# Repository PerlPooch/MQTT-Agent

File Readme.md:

# Spencer MQTT Agent

Please see the [Project Website](https://home.marcspencer.com/mqtt-agent/) for detailed information, full API, and build details. 

## MQTT Topic

	spencer/<ID>/<device>
		<ID> := unique MAC address of device
		<device> := temperature|status|relay
		
## Payload (JSON object):

	{
		"command": "fetch"|"set-rate"|"set"
		"rate": int: seconds between updates|duration
		"device-num": int: 0-based index of device 
		"state": "on"|"off"|"pulse"
	}

	command == "fetch"
		Causes agent to publish information for <device>

	command == "set-rate"
		Sets update rate for <device> to rate in rate. <device> can be temperature, status or relay

	command == "set"
		Sets <device> at index device-num to state. <device> can be relay. <state> can be on, off, or pulse.
		
## Examples:

	spencer/FC:F5:C4:AB:56:24/temperature {"command":"set-rate", "rate":"120"}
		Set the update rate for temperature reports to be 120 seconds

	spencer/FC:F5:C4:AB:56:24/status {"command":"set-rate", "rate":"300"}
		Set the update rate for status reports to be 300 seconds

	spencer/FC:F5:C4:AB:56:24/relay {"command":"set", "device-num":"1", "state":"on"}
		Turn on relay 0

	spencer/FC:F5:C4:AB:56:24/relay {"command":"set", "device-num":"1", "state":"off"}
		Turn off relay 1

	spencer/FC:F5:C4:AB:56:24/relay {"command":"set", "device-num":"0", "state":"pulse"}
		Pulse relay 0

	spencer/FC:F5:C4:AB:56:24/relay {"command":"set-rate", "rate":"200"}
		Set relay pulse duration to 100ms

	spencer/FC:F5:C4:AB:56:24/temperature {"command":"fetch"}
		Request publish of temperature

	spencer/FC:F5:C4:AB:56:24/status {"command":"fetch"}
		Request publish of input status

	spencer/FC:F5:C4:AB:56:24/relay {"command":"fetch"}
		Request publish of relay status

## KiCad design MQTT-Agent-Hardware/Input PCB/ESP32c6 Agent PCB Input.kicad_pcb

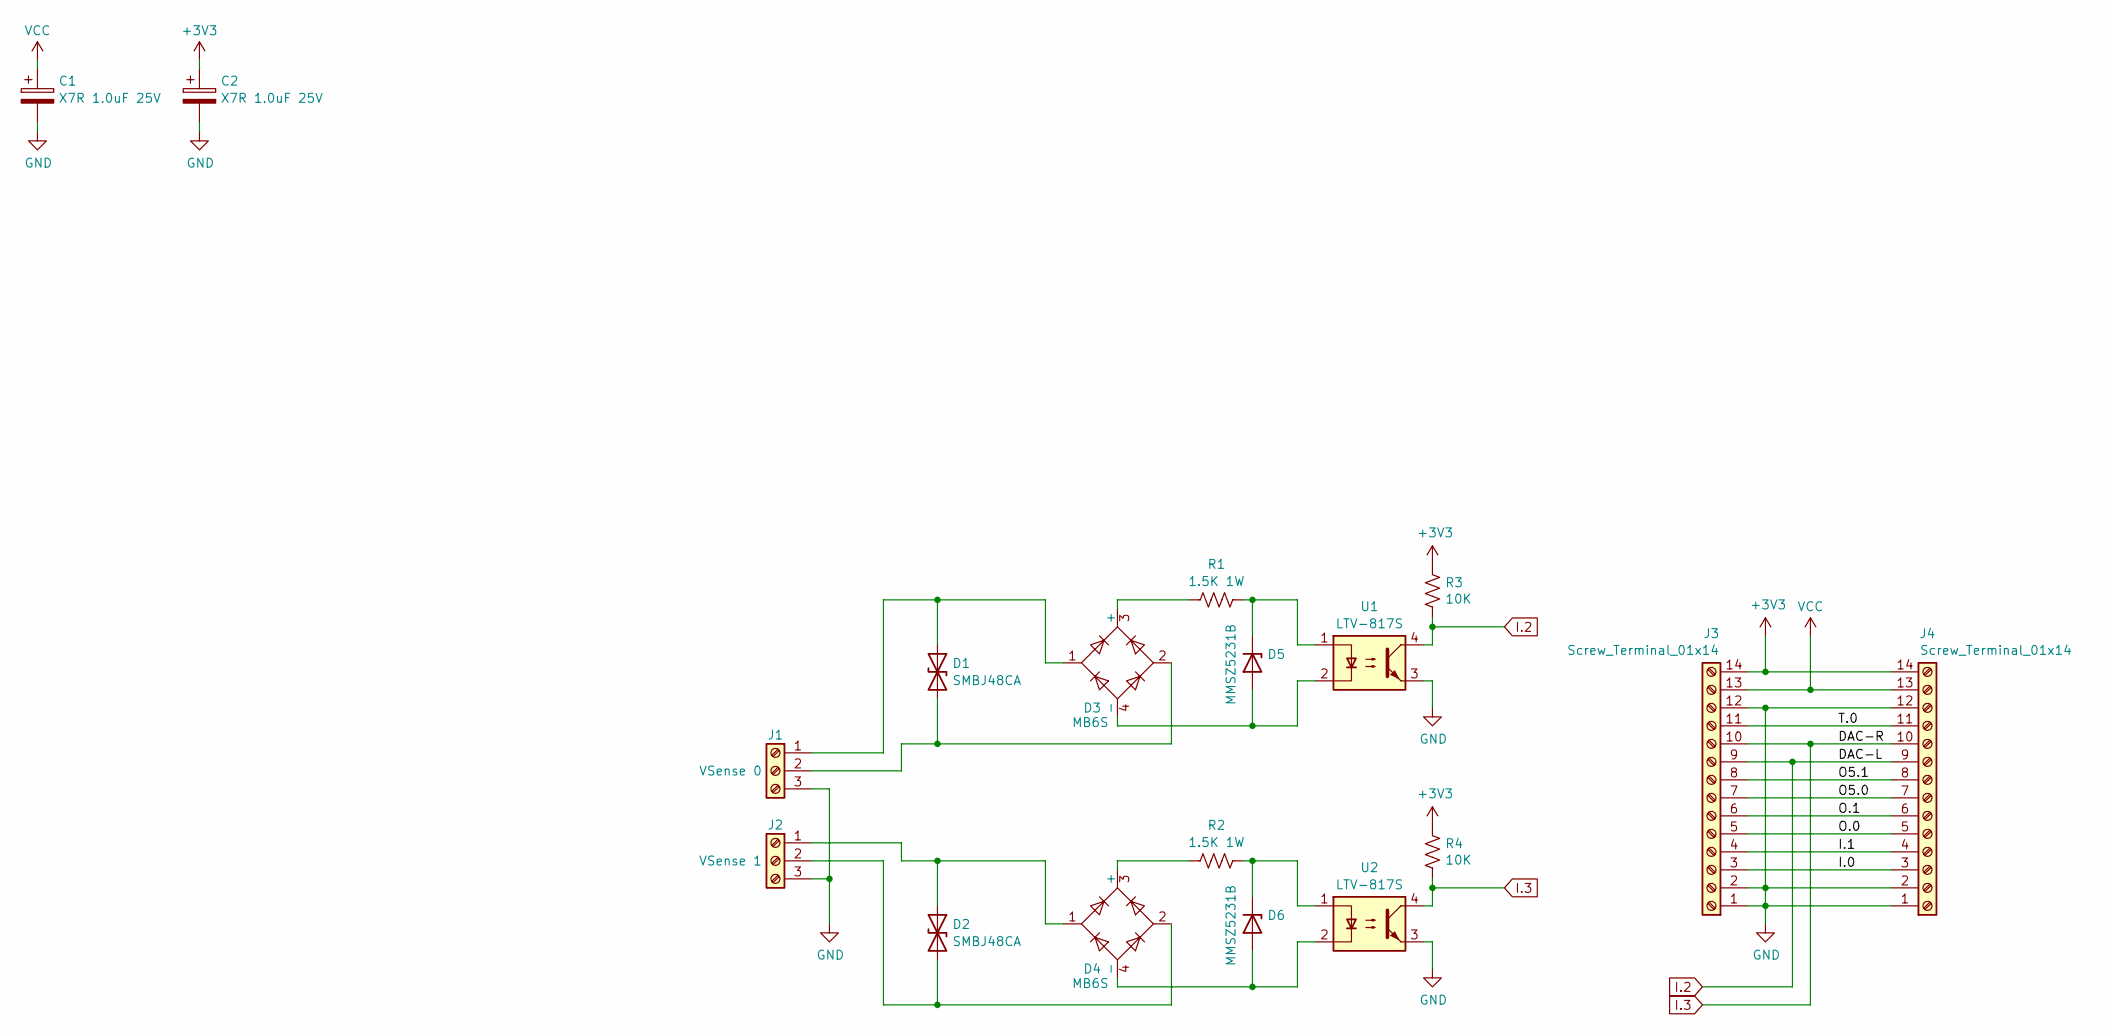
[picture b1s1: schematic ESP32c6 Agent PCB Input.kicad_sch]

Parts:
C1, C2: X7R 1.0uF 25V; C_0805_2012Metric_Pad1.18x1.45mm_HandSolder
D1, D2: SMBJ48CA; D_SMB
D3, D4: MB6S; TO-269AA
D5, D6: MMSZ5231B; Nexperia_CFP3_SOD-123W
J1: VSense 0; Molex_KK-254_AE-6410-03A_1x03_P2.54mm_Vertical
J2: VSense 1; Molex_KK-254_AE-6410-03A_1x03_P2.54mm_Vertical
J3: Screw_Terminal_01x14; Connector SIP-14-Soldertail-L
J4: Screw_Terminal_01x14; Connector SIP-14-Soldertail-R
R1, R2: 1.5K 1W; R_2512_6332Metric_Pad1.40x3.35mm_HandSolder
R3, R4: 10K; R_1206_3216Metric_Pad1.30x1.75mm_HandSolder
U1, U2: LTV-817S; SMDIP-4_W9.53mm

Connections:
+3V3: C2.1, J3.14, J4.14, R3.1, R4.1
/I.0: J3.3, J4.3
/I.1: J3.4, J4.4
/O5.0: J3.7, J4.7
/O5.1: J3.8, J4.8
/O.0: J3.5, J4.5
/O.1: J3.6, J4.6
/T.0: J3.11, J4.11
GND: C1.2, C2.2, J1.3, J2.3, J3.1, J3.2, J3.12, J4.1, J4.2, J4.12, U1.3, U2.3
I.2: J3.9, J4.9, R3.2, U1.4
I.3: J3.10, J4.10, R4.2, U2.4
unnamed: D1.1 (A1), D3.1, J1.1
unnamed: D1.2 (A2), D3.2, J1.2
unnamed: D2.1 (A1), D4.1, J2.1
unnamed: D2.2 (A2), D4.2, J2.2
unnamed: D3.3 (+), R1.1
unnamed: D3.4 (-), D5.2 (A), U1.2
unnamed: D4.3 (+), R2.1
unnamed: D4.4 (-), D6.2 (A), U2.2
unnamed: D5.1 (K), R1.2, U1.1
unnamed: D6.1 (K), R2.2, U2.1
VCC: C1.1, J3.13, J4.13

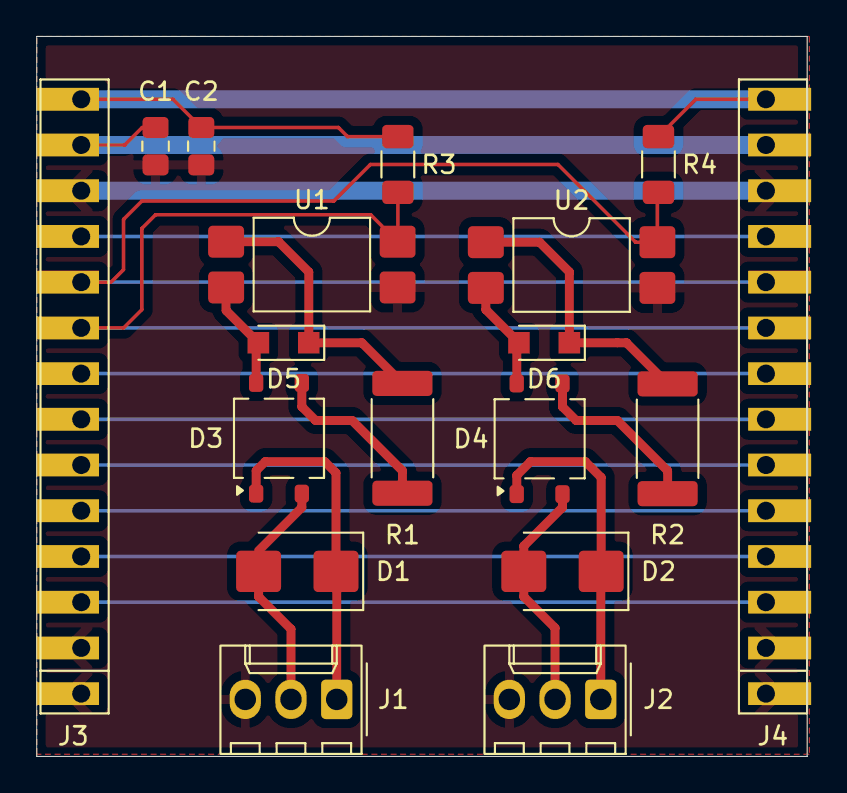
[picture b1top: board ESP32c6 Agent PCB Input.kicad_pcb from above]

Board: 2 copper layers, 42.8 x 40.0 mm, 18 parts (0 on the bottom side), 22 nets.

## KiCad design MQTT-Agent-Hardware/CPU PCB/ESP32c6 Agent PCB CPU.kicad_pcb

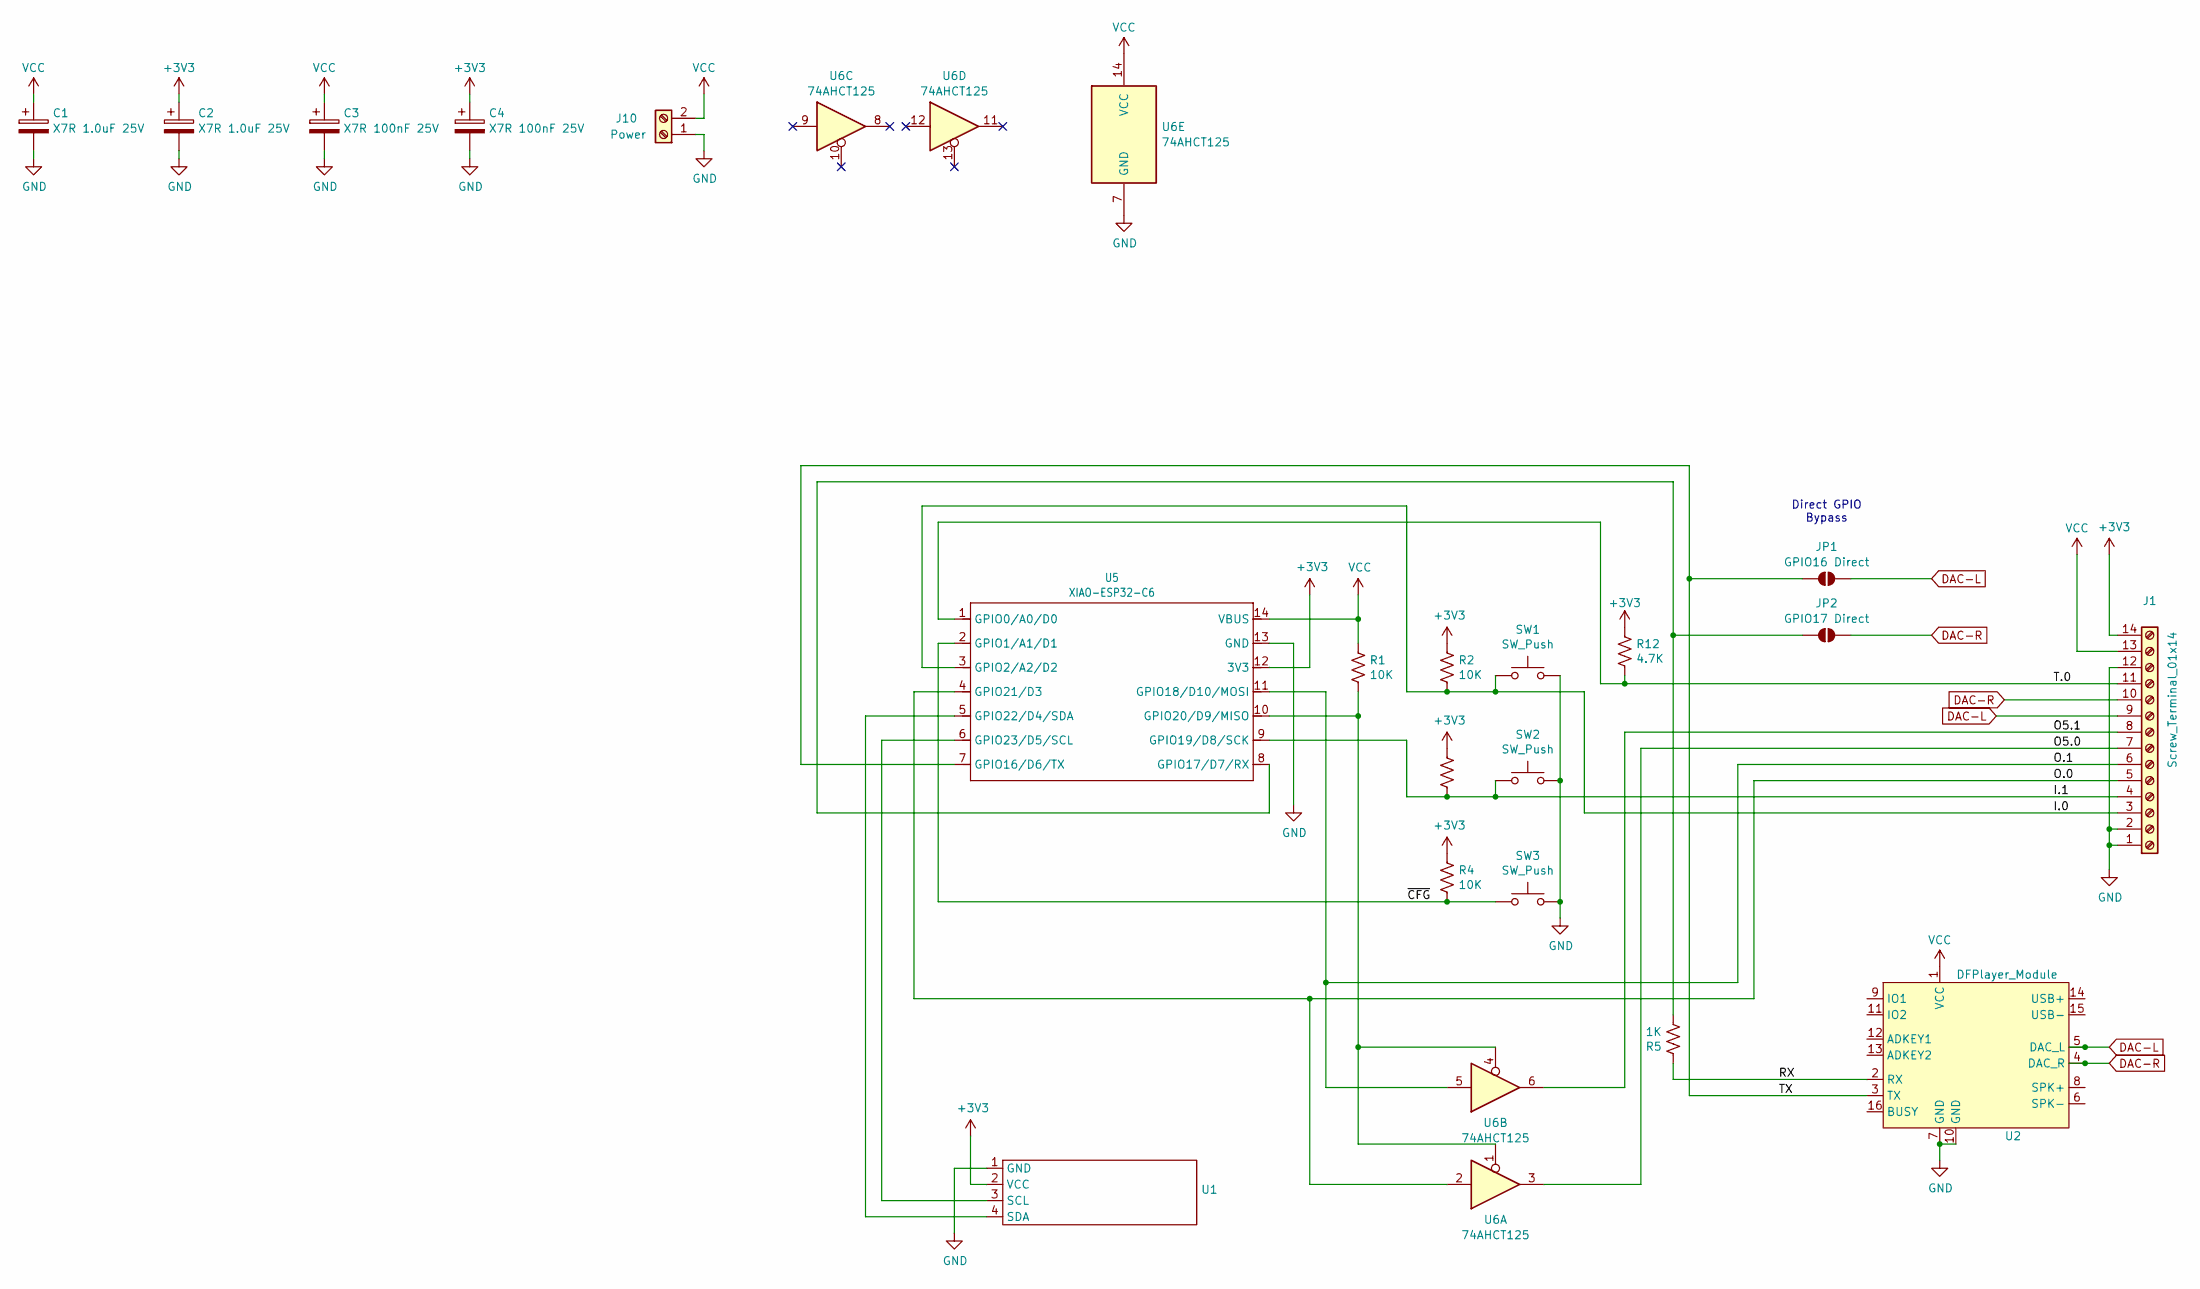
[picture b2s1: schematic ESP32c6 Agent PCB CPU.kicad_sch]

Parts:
C1, C2: X7R 1.0uF 25V; C_0805_2012Metric_Pad1.18x1.45mm_HandSolder
C3, C4: X7R 100nF 25V; C_1206_3216Metric_Pad1.33x1.80mm_HandSolder
J1: Screw_Terminal_01x14; Connector SIP-14-Soldertail-R
J10: Power; Molex_KK-254_AE-6410-02A_1x02_P2.54mm_Vertical
JP1: GPIO16 Direct; SolderJumper-2_P1.3mm_Open_Pad1.0x1.5mm
JP2: GPIO17 Direct; SolderJumper-2_P1.3mm_Open_Pad1.0x1.5mm
R1, R2, R3, R4: 10K; R_1206_3216Metric_Pad1.30x1.75mm_HandSolder
R5: 1K; R_1206_3216Metric_Pad1.30x1.75mm_HandSolder
R12: 4.7K; R_1206_3216Metric_Pad1.30x1.75mm_HandSolder
SW1, SW2, SW3: SW_Push; SW_PUSH_6mm_H4.3mm
U1: SSD1306-128x32_Borderless
U2: DFPlayer_Module; DFPlayer
U5: XIAO-ESP32-C6; XIAO-ESP32C6-DIP
U6: 74AHCT125; SSOP-14_5.3x6.2mm_P0.65mm

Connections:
+3V3: C2.1, C4.1, J1.14, R2.1, R3.1, R4.1, R12.1, U1.2 (VCC), U5.12 (3V3)
/I.0: J1.3, R2.2, SW1.1, U5.3 (GPIO2/A2/D2)
/I.1: J1.4, R3.2, SW2.1, U5.9 (GPIO19/D8/SCK)
/O5.0: J1.7, U6.3
/O5.1: J1.8, U6.6
/O.0: J1.5, U5.4 (GPIO21/D3), U6.2
/O.1: J1.6, U5.11 (GPIO18/D10/MOSI), U6.5
/RX: R5.1, U2.2 (RX)
/T.0: J1.11, R12.2, U5.1 (GPIO0/A0/D0)
/TX: JP1.1 (A), U2.3 (TX), U5.7 (GPIO16/D6/TX)
/~CFG: R4.2, SW3.1, U5.2 (GPIO1/A1/D1)
DAC-L: J1.9, JP1.2 (B), U2.5 (DAC_L)
DAC-R: J1.10, JP2.2 (B), U2.4 (DAC_R)
GND: C1.2, C2.2, C3.2, C4.2, J1.1, J1.2, J1.12, J10.1, SW1.2, SW2.2, SW3.2, U1.1 (GND), U2.7 (GND), U2.10 (GND), U5.13 (GND), U6.7 (GND)
unnamed: JP2.1 (A), R5.2, U5.8 (GPIO17/D7/RX)
unnamed: U1.3 (SCL), U5.6 (GPIO23/D5/SCL)
unnamed: U1.4 (SDA), U5.5 (GPIO22/D4/SDA)
unnamed: R1.2, U5.10 (GPIO20/D9/MISO), U6.1, U6.4
VCC: C1.1, C3.1, J1.13, J10.2, R1.1, U2.1 (VCC), U5.14 (VBUS), U6.14 (VCC)

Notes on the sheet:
Direct GPIO Bypass

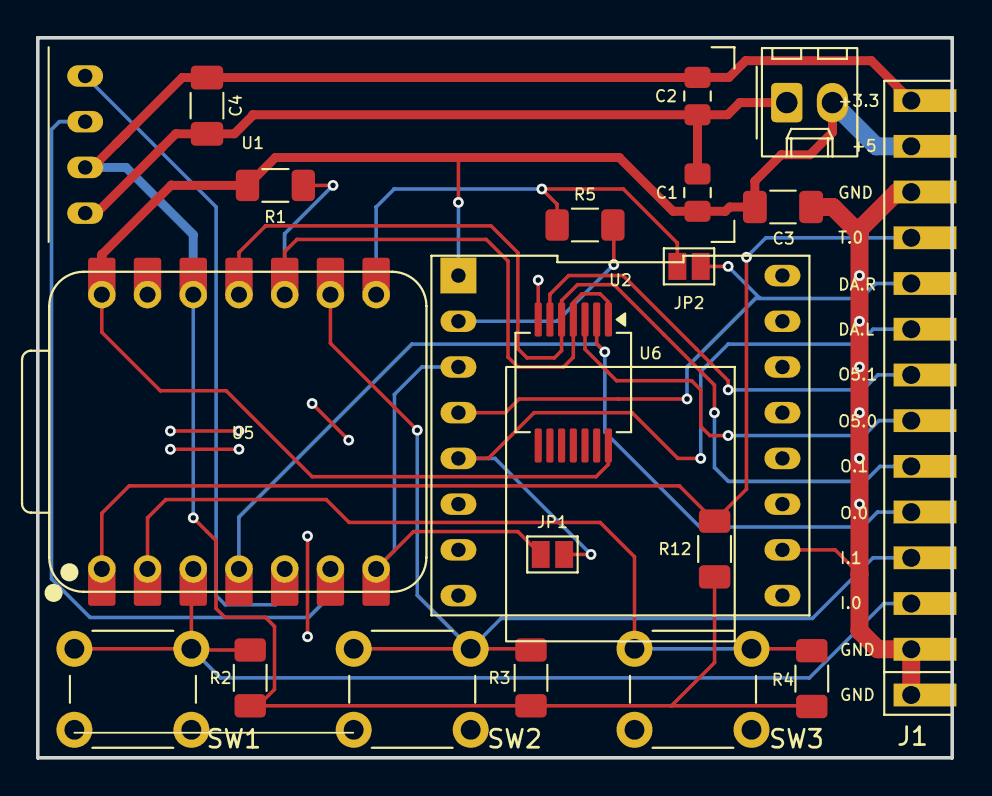
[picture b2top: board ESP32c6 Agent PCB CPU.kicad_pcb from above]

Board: 2 copper layers, 50.8 x 40.0 mm, 21 parts (0 on the bottom side), 19 nets.

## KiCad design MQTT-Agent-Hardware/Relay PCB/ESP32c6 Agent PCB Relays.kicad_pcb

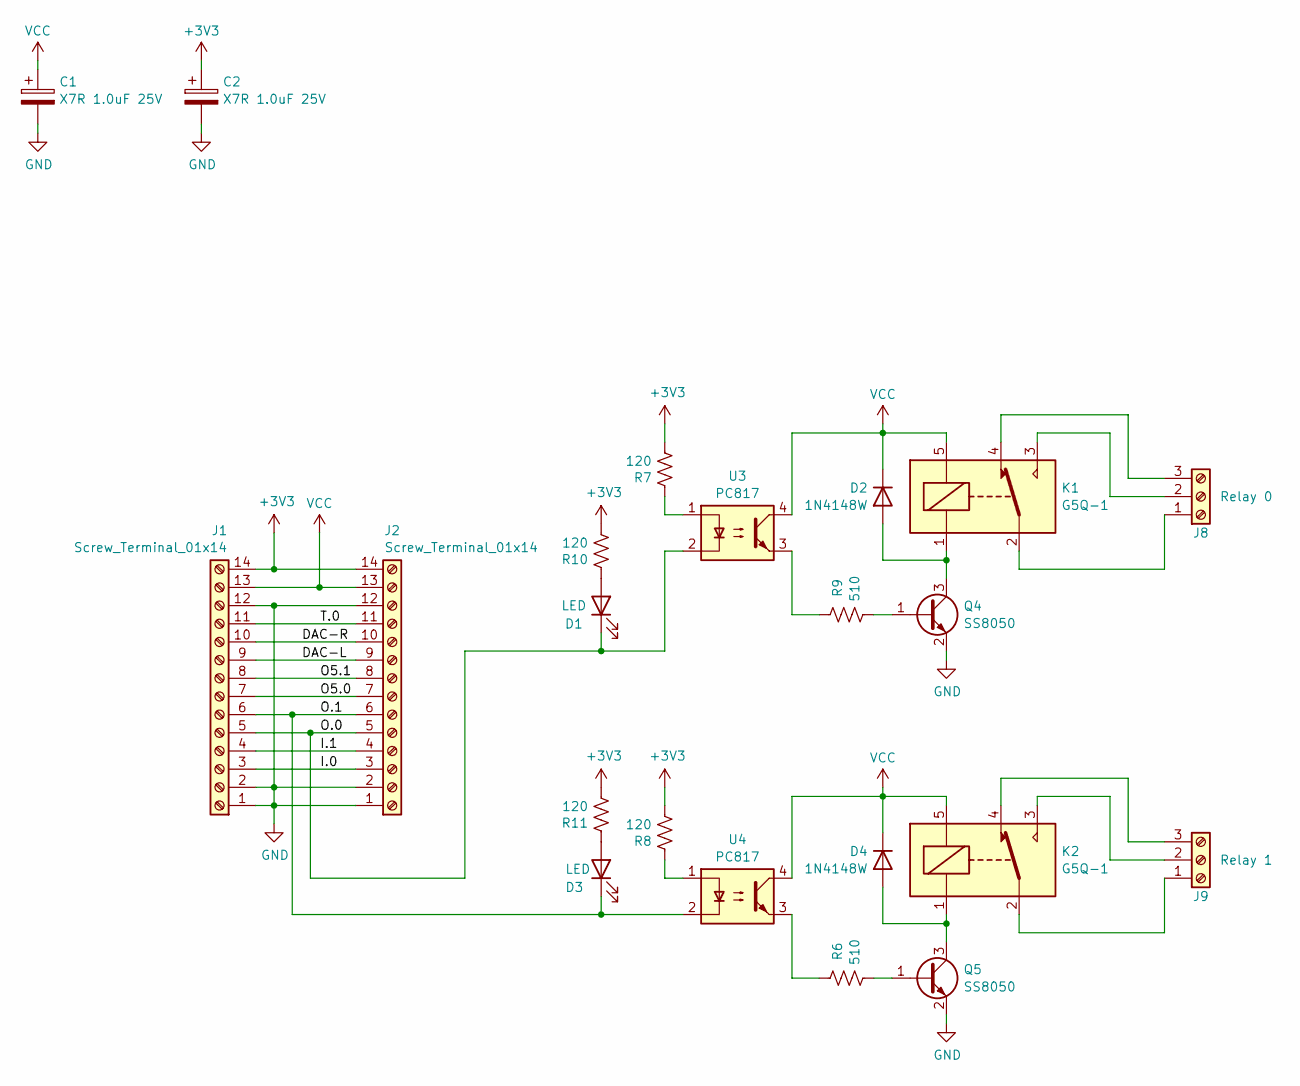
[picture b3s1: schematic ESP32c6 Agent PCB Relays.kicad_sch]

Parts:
C1, C2: X7R 1.0uF 25V; C_0805_2012Metric_Pad1.18x1.45mm_HandSolder
D1, D3: LED; LED_1206_3216Metric_Pad1.42x1.75mm_HandSolder
D2, D4: 1N4148W; D_SOD-123
J1: Screw_Terminal_01x14; Connector SIP-14-Soldertail-L
J2: Screw_Terminal_01x14; Connector SIP-14-Soldertail-R
J8: Relay 0; Molex_KK-254_AE-6410-03A_1x03_P2.54mm_Vertical
J9: Relay 1; Molex_KK-254_AE-6410-03A_1x03_P2.54mm_Vertical
K1, K2: G5Q-1; Relay_SPDT_Omron-G5Q-1
Q4, Q5: SS8050; SOT-23
R6, R9: 510; R_1206_3216Metric_Pad1.30x1.75mm_HandSolder
R7, R8, R10, R11: 120; R_1206_3216Metric_Pad1.30x1.75mm_HandSolder
U3, U4: PC817; DIP-4_W7.62mm

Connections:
+3V3: C2.1, J1.14, J2.14, R7.2, R8.2, R10.2, R11.2
/DAC-L: J1.9, J2.9
/DAC-R: J1.10, J2.10
/I.0: J1.3, J2.3
/I.1: J1.4, J2.4
/O5.0: J1.7, J2.7
/O5.1: J1.8, J2.8
/O.0: D1.1 (K), J1.5, J2.5, U3.2
/O.1: D3.1 (K), J1.6, J2.6, U4.2
/T.0: J1.11, J2.11
GND: C1.2, C2.2, J1.1, J1.2, J1.12, J2.1, J2.2, J2.12, Q4.2 (E), Q5.2 (E)
unnamed: D1.2 (A), R10.1
unnamed: D2.2 (A), K1.1, Q4.3 (C)
unnamed: D3.2 (A), R11.1
unnamed: D4.2 (A), K2.1, Q5.3 (C)
unnamed: J8.1, K1.2
unnamed: J8.2, K1.3
unnamed: J8.3, K1.4
unnamed: J9.1, K2.2
unnamed: J9.2, K2.3
unnamed: J9.3, K2.4
unnamed: Q4.1 (B), R9.2
unnamed: Q5.1 (B), R6.2
unnamed: R6.1, U4.3
unnamed: R7.1, U3.1
unnamed: R8.1, U4.1
unnamed: R9.1, U3.3
VCC: C1.1, D2.1 (K), D4.1 (K), J1.13, J2.13, K1.5, K2.5, U3.4, U4.4

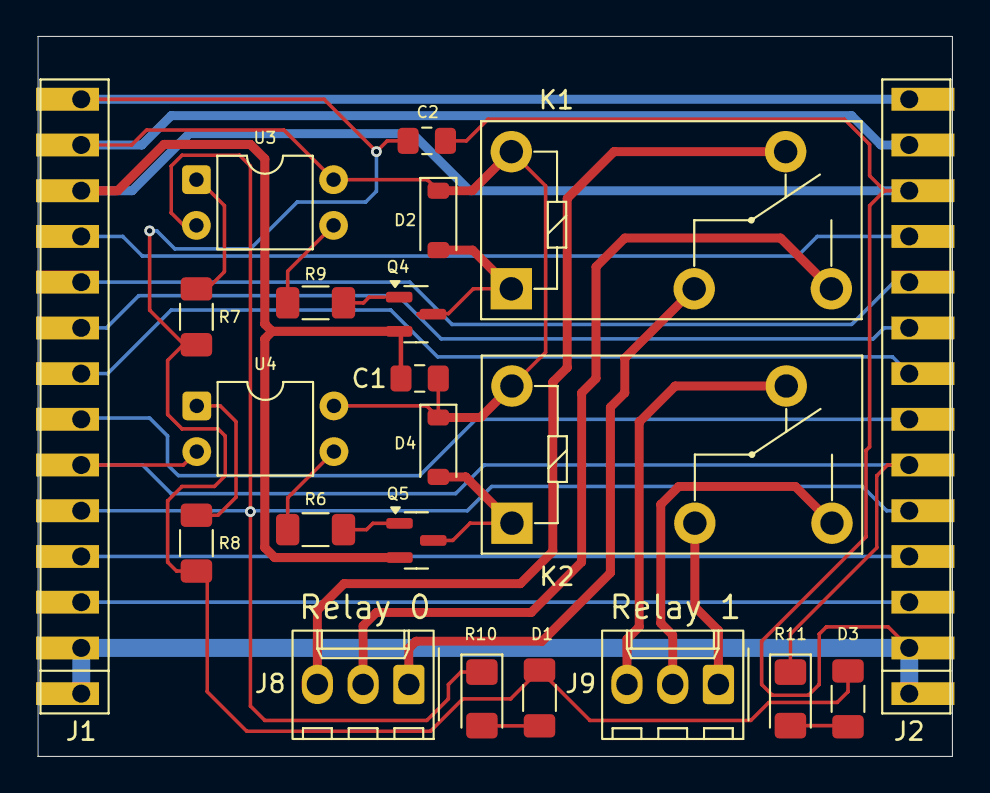
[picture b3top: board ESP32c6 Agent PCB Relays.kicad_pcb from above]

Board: 2 copper layers, 50.8 x 40.0 mm, 22 parts (0 on the bottom side), 28 nets.

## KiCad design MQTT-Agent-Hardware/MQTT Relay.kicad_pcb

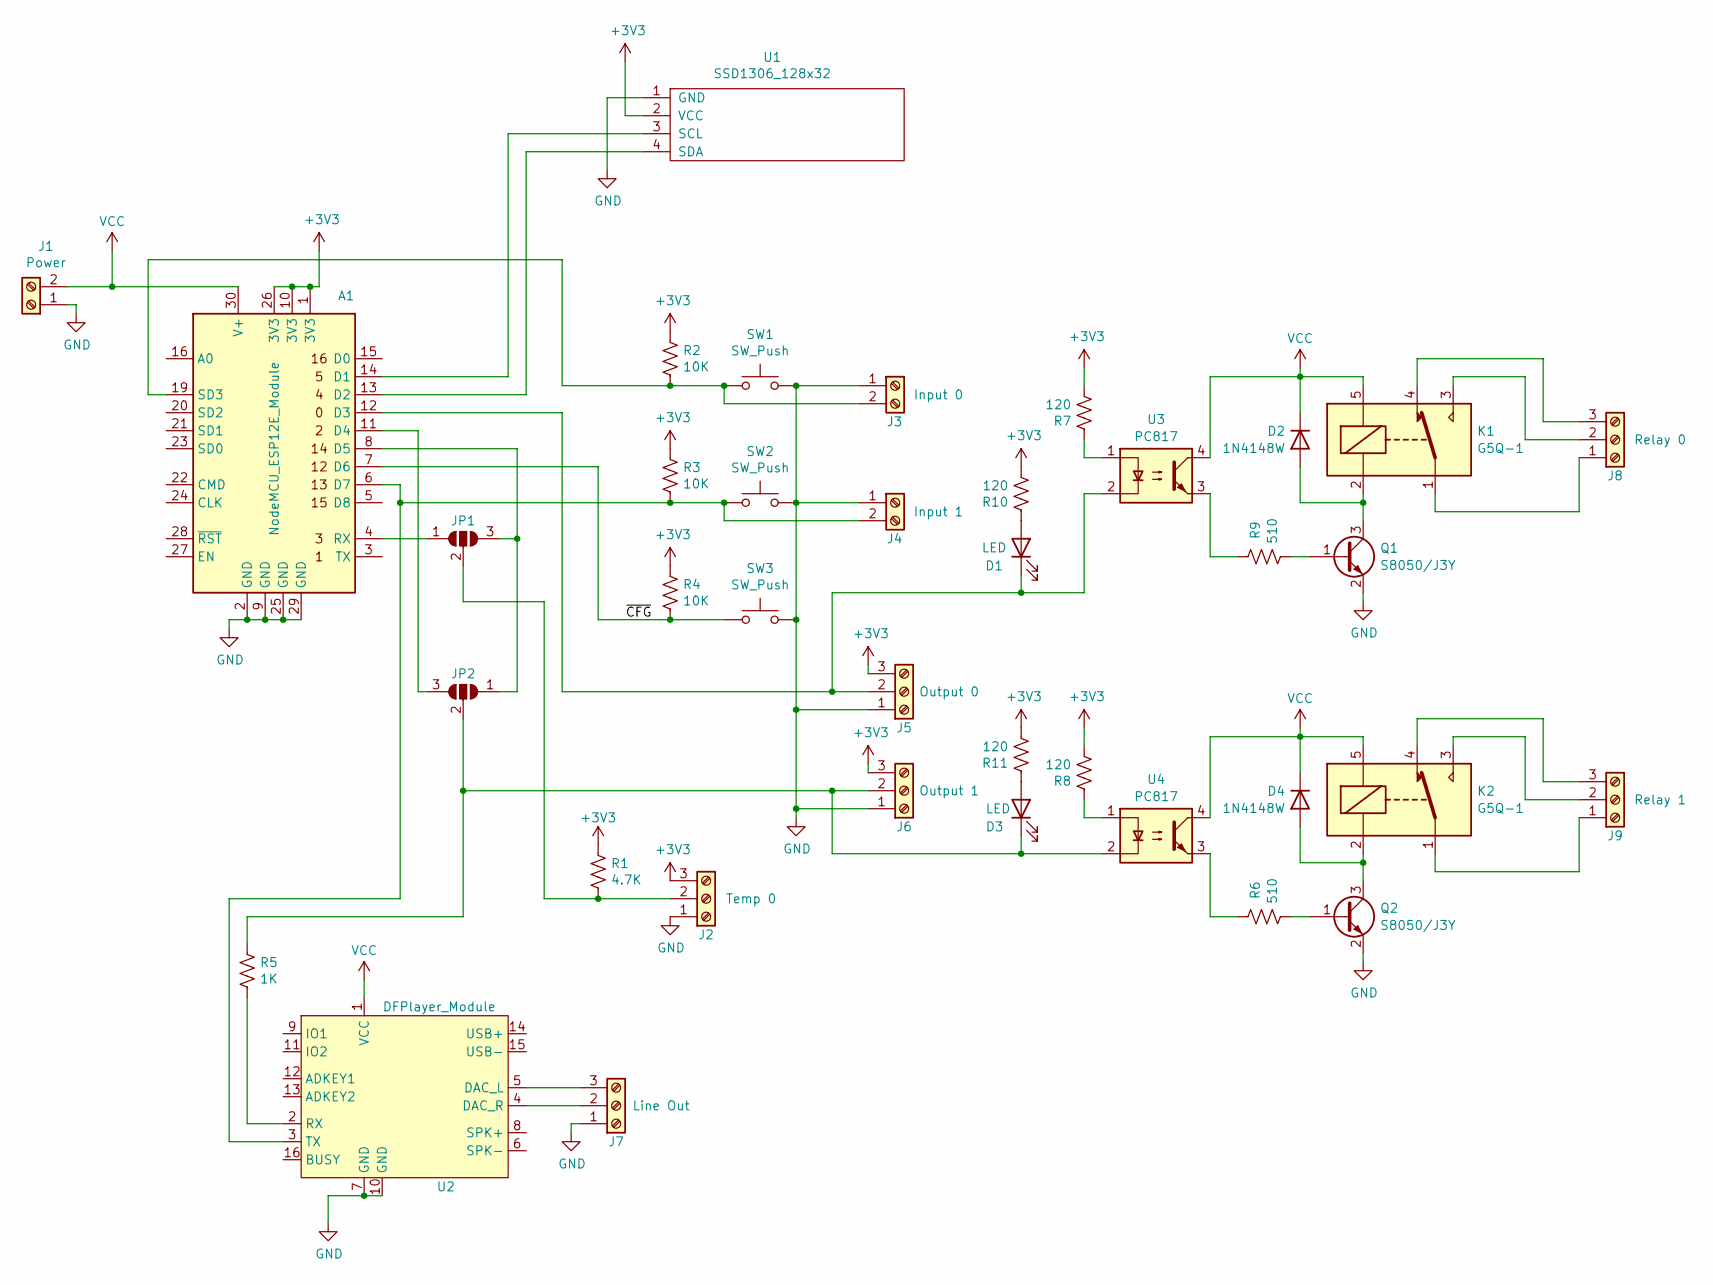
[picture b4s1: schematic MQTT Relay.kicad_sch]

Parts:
A1: NodeMCU_ESP12E_Module; NodeMCU
D1, D3: LED; LED_1206_3216Metric_Pad1.42x1.75mm_HandSolder
D2, D4: 1N4148W; D_SOD-123
J1: Power; TerminalBlock_Phoenix_MPT-0,5-2-2.54_1x02_P2.54mm_Horizontal
J2: Temp 0; TerminalBlock_Phoenix_MPT-0,5-3-2.54_1x03_P2.54mm_Horizontal
J3: Input 0; TerminalBlock_Phoenix_MPT-0,5-2-2.54_1x02_P2.54mm_Horizontal
J4: Input 1; TerminalBlock_Phoenix_MPT-0,5-2-2.54_1x02_P2.54mm_Horizontal
J5: Output 0; TerminalBlock_Phoenix_MPT-0,5-3-2.54_1x03_P2.54mm_Horizontal
J6: Output 1; TerminalBlock_Phoenix_MPT-0,5-3-2.54_1x03_P2.54mm_Horizontal
J7: Line Out; TerminalBlock_Phoenix_MPT-0,5-3-2.54_1x03_P2.54mm_Horizontal
J8: Relay 0; TerminalBlock_Phoenix_MPT-0,5-3-2.54_1x03_P2.54mm_Horizontal
J9: Relay 1; TerminalBlock_Phoenix_MPT-0,5-3-2.54_1x03_P2.54mm_Horizontal
JP1: T-0; SolderJumper-3_P1.3mm_Open_Pad1.0x1.5mm_NumberLabels
JP2: R-1; SolderJumper-3_P1.3mm_Open_Pad1.0x1.5mm_NumberLabels
K1, K2: G5Q-1; Relay_SPDT_SANYOU_SRD_Series_Form_C
Q1, Q2: S8050/J3Y; SOT-23-3
R1: 4.7K; R_1206_3216Metric_Pad1.30x1.75mm_HandSolder
R2, R3, R4: 10K; R_1206_3216Metric_Pad1.30x1.75mm_HandSolder
R5: 1K; R_1206_3216Metric_Pad1.30x1.75mm_HandSolder
R6, R9: 510; R_1206_3216Metric_Pad1.30x1.75mm_HandSolder
R7, R8, R10, R11: 120; R_1206_3216Metric_Pad1.30x1.75mm_HandSolder
SW1, SW2, SW3: SW_Push; SW_PUSH_6mm_H4.3mm
U1: SSD1306_128x32; PinHeader_1x04_P2.54mm_Vertical
U2: DFPlayer_Module; Module_DIP16_17.8mm
U3, U4: PC817; DIP-4_W7.62mm

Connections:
+3V3: A1.1 (3V3), A1.10 (3V3), A1.26 (3V3), J2.3, J5.3, J6.3, R1.1, R2.1, R3.1, R4.1, R7.2, R8.2, R10.2, R11.2, U1.2 (VCC)
/~CFG: A1.7 (D6), R4.2, SW3.1
GND: A1.2 (GND), A1.9 (GND), A1.25 (GND), A1.29 (GND), J1.1, J2.1, J3.1, J4.1, J5.1, J6.1, J7.1, Q1.2 (E), Q2.2 (E), SW1.2, SW2.2, SW3.2, U1.1 (GND), U2.7 (GND), U2.10 (GND)
unnamed: A1.14 (D1), U1.3 (SCL)
unnamed: A1.13 (D2), U1.4 (SDA)
unnamed: A1.12 (D3), D1.1 (K), J5.2, U3.2
unnamed: A1.11 (D4), JP2.3 (B)
unnamed: A1.8 (D5), JP1.3 (B), JP2.1 (A)
unnamed: A1.6 (D7), J4.2, R3.2, SW2.1, U2.3 (TX)
unnamed: A1.4 (RX), JP1.1 (A)
unnamed: A1.19 (SD3), J3.2, R2.2, SW1.1
unnamed: D1.2 (A), R10.1
unnamed: D2.2 (A), K1.2, Q1.3 (C)
unnamed: D3.2 (A), R11.1
unnamed: D3.1 (K), J6.2, JP2.2 (C), R5.1, U4.2
unnamed: D4.2 (A), K2.2, Q2.3 (C)
unnamed: J2.2, JP1.2 (C), R1.2
unnamed: J7.2, U2.4 (DAC_R)
unnamed: J7.3, U2.5 (DAC_L)
unnamed: J8.1, K1.1
unnamed: J8.2, K1.3
unnamed: J8.3, K1.4
unnamed: J9.1, K2.1
unnamed: J9.2, K2.3
unnamed: J9.3, K2.4
unnamed: Q1.1 (B), R9.2
unnamed: Q2.1 (B), R6.2
unnamed: R6.1, U4.3
unnamed: R7.1, U3.1
unnamed: R8.1, U4.1
unnamed: R9.1, U3.3
unnamed: R5.2, U2.2 (RX)
VCC: A1.30 (V+), D2.1 (K), D4.1 (K), J1.2, K1.5, K2.5, U2.1 (VCC), U3.4, U4.4

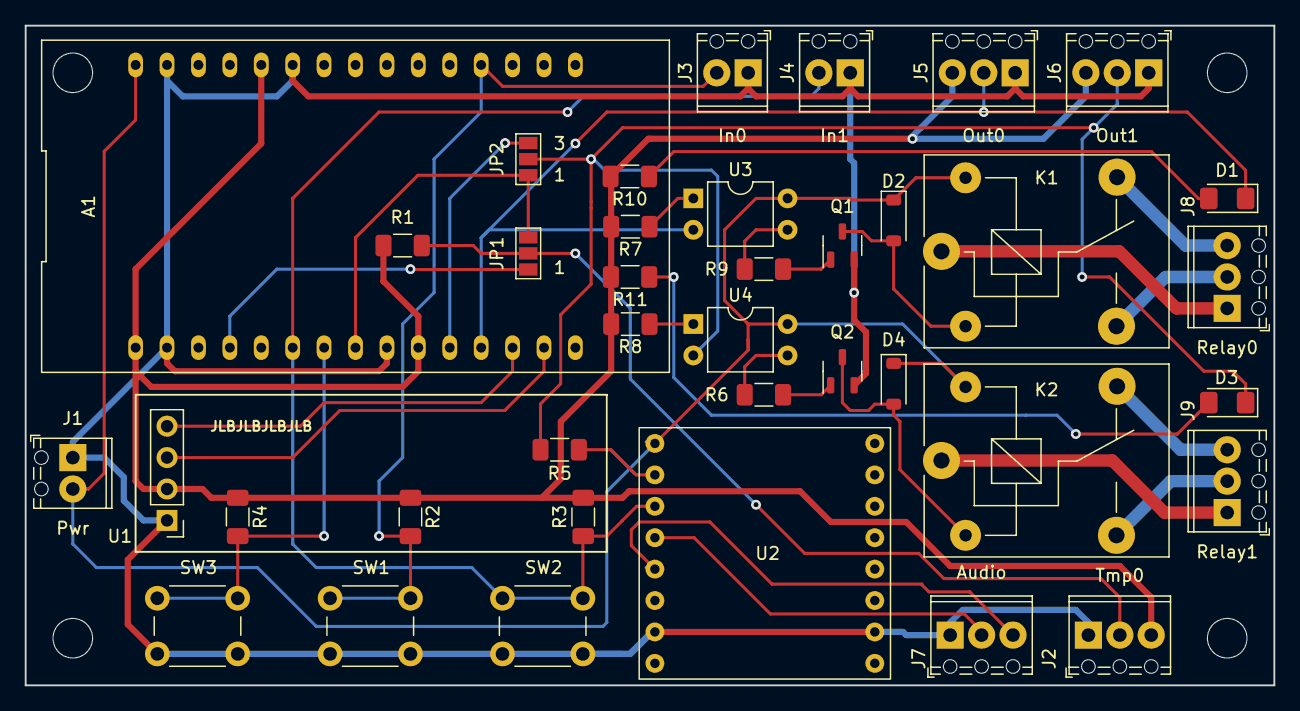
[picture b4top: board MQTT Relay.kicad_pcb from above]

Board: 2 copper layers, 101.0 x 53.3 mm, 38 parts (0 on the bottom side), 33 nets.

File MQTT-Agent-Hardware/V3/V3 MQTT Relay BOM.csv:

"Id";"Designator";"Footprint";"Quantity";"Designation";"Supplier and ref";
1;"J1";"TerminalBlock_Phoenix_MPT-0,5-2-2.54_1x02_P2.54mm_Horizontal";1;"Power";;;
2;"J2";"TerminalBlock_Phoenix_MPT-0,5-3-2.54_1x03_P2.54mm_Horizontal";1;"Temp 0";;;
3;"J3";"TerminalBlock_Phoenix_MPT-0,5-2-2.54_1x02_P2.54mm_Horizontal";1;"Input 0";;;
4;"J4";"TerminalBlock_Phoenix_MPT-0,5-2-2.54_1x02_P2.54mm_Horizontal";1;"Input 1";;;
5;"J5";"TerminalBlock_Phoenix_MPT-0,5-3-2.54_1x03_P2.54mm_Horizontal";1;"Output 0";;;
6;"J6";"TerminalBlock_Phoenix_MPT-0,5-3-2.54_1x03_P2.54mm_Horizontal";1;"Output 1";;;
7;"R1";"R_1206_3216Metric_Pad1.30x1.75mm_HandSolder";1;"4.7K";;;
8;"R3,R4,R2";"R_1206_3216Metric_Pad1.30x1.75mm_HandSolder";3;"10K";;;
9;"SW1,SW2,SW3";"SW_PUSH_6mm_H4.3mm";3;"SW_Push";;;
10;"A1";"NodeMCU";1;"NodeMCU_ESP12E_Module";;;
11;"U1";"PinHeader_1x04_P2.54mm_Vertical";1;"SSD1306_128x32";;;
12;"D1,D3";"LED_0603_1608Metric_Pad1.05x0.95mm_HandSolder";2;"LED";;;
13;"D2,D4";"D_SOD-123";2;"1N4148W";;;
14;"Q2,Q1";"SOT-23-3";2;"S8050/J3Y";;;
15;"J7";"TerminalBlock_Phoenix_MPT-0,5-3-2.54_1x03_P2.54mm_Horizontal";1;"Line Out";;;
16;"J8";"TerminalBlock_Phoenix_MPT-0,5-3-2.54_1x03_P2.54mm_Horizontal";1;"Relay 0";;;
17;"JP1";"SolderJumper-3_P1.3mm_Open_Pad1.0x1.5mm_NumberLabels";1;"T-0";;;
18;"U4,U3";"DIP-4_W7.62mm";2;"PC817";;;
19;"R7,R5,R8";"R_1206_3216Metric_Pad1.30x1.75mm_HandSolder";3;"1K";;;
20;"K2,K1";"Relay_SPDT_SANYOU_SRD_Series_Form_C";2;"G5Q-1";;;
21;"J9";"TerminalBlock_Phoenix_MPT-0,5-3-2.54_1x03_P2.54mm_Horizontal";1;"Relay 1";;;
22;"R6,R9";"R_1206_3216Metric_Pad1.30x1.75mm_HandSolder";2;"510";;;
23;"JP2";"SolderJumper-3_P1.3mm_Open_Pad1.0x1.5mm_NumberLabels";1;"R-1";;;
24;"U2";"Module_DIP16_17.8mm";1;"DFPlayer_Module";;;

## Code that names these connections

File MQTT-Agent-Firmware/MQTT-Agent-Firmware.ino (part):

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	#endif
	#define PIN_LED				LED_BUILTIN
	// I2C OLED
	#define PIN_I2C_SDA			SDA    // D4 / GPIO22
	#define PIN_I2C_SCL			SCL    // D5 / GPIO23
	// DFPlayer
	#define DFP_UART_NUM		1
	#define PIN_DFP_TX			D6    // GPIO16
	#define PIN_DFP_RX			D7    // GPIO17
	// Inputs
	#define PIN_RESET_WIFI		D1  // GPIO1  (button to GND, INPUT_PULLUP)
	#ifdef USE_STATUS_0
		#define PIN_STATUS_0	D2  // GPIO2  (INPUT_PULLUP)
	#endif
	#ifdef USE_STATUS_1
		#define PIN_STATUS_1 	D8	// GPIO19
	#endif
	// 1-wire temp
	#define PIN_TEMP_0			D0   // GPIO0  (1-wire)
	// Relay
	#if defined(USE_RELAY_0) || defined(PLAY_TRIGGER_RELAY_0)
		#define PIN_RELAY_0		D3   // GPIO21
	#endif
	#ifdef USE_RELAY_1
		#define PIN_RELAY_1 	D10
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
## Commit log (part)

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2020-11-07 Initial add of Arduino Firmware
2020-11-07 Initial add of KiCAD Project
2022-01-06 Added Readme
2023-07-31 Cleaned up overall messaging
2023-07-31 Modularized and Sound
    Added modular configuration. Added support for Midi and DFPlayer
2023-07-31 Added DFPlayer support
2023-11-23 Version 3.0 Board
    Integrated relays and SMD
2024-01-02 Added Relays onBoard
2024-01-02 Version 1.6
    Fixed (I hope) configuration loss when power fails. Dumb.
    Cleaned up configuration reporting and logic.
2025-10-31 Expansion and cleanup
2026-01-04 Fixed buffer overrun when subscribing to MQTT. Added automatic N-day reboot
2026-01-05 Cleaned up some bounds issues. Cleanup of Serial stream.
2026-01-05 Cleaned up more bounds issues.
2026-01-05 Cleaned up more type issues to save stack churn.
2026-01-06 Fixed WiFi reconnect logic. Finally. Automatic reconnection if/when WiFi dissappears.
2026-02-15 General cleanup
2026-02-15 Renamed 8266_MQTTAgent to MQTT-Agent-Firmware as it is no-longer board-specific.
2026-02-15 Renaming MQTT Relay KiCAD Project to MQTT-Agent-Hardware
2026-02-15 Cleanup
2026-02-15 Removed accidental zips
2026-02-15 Reorganize Gerbers into a subfolder
2026-02-15 Transitioning to ESP32 and modular PCB approach
2026-02-16 Renamed 8266_MQTTAgent.ino too MQTT-Agent.ino
2026-02-16 Added ESP32c6 Support
2026-02-16 Renamed to MQTT-Agent-Firmware
2026-02-16 Removed. Obsolete.
2026-02-21 More cleanup
    Cleaned up WiFi Connection failures.
    Fixed AP name
2026-02-21 Added multi-sensor support for 1-wire temperature
2026-02-26 Added average temperature
2026-02-26 Added 10-second button → reboot
2026-03-08 Cleanup and Finalize.
    Updated footprints.
    cleaned up silkscreen.
    Changed schematic to B-size
2026-03-09 Generated Gerbers
2026-03-09 Initial Create
2026-03-21 Added /ui endpoint
    Added a full HTML configuration and status endpoint
2026-03-23 Added configurable relay pulse timing with relayPulseDuration
2026-03-23 Added MQTT example for relay pulse duration
2026-04-24 Abstracted MDS_Display out to separate class
2026-04-24 Abstracted Config to MDS_Config
2026-05-09 Updated Readme.

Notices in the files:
MQTT-Agent-Hardware/CPU PCB/ESP32c6 Agent PCB CPU.kicad_pcb:
(c) 2026 Marc D. Spencer
MQTT-Agent-Hardware/MQTT Relay.kicad_pcb:
(c) 2023 Marc D. Spencer
